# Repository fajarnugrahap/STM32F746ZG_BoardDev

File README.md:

# STM32F746ZG_Minimum-System
There are some embedded features in this minimum system like UART, I2C, CAN Bus, QuadSPI Flash, Ext. SDRAM, SPI for LCD TFT/Oled Support, USB-C and GPIO port                                              

First thing first I set the pinout configuration of STM32F746ZG by using CubeMx tools in STM32CubeIDE
                                                          
I'm using KiCadV6+ to design this minimum system. There is some additional component to support some peripheral/bus. You can check the component library folder.

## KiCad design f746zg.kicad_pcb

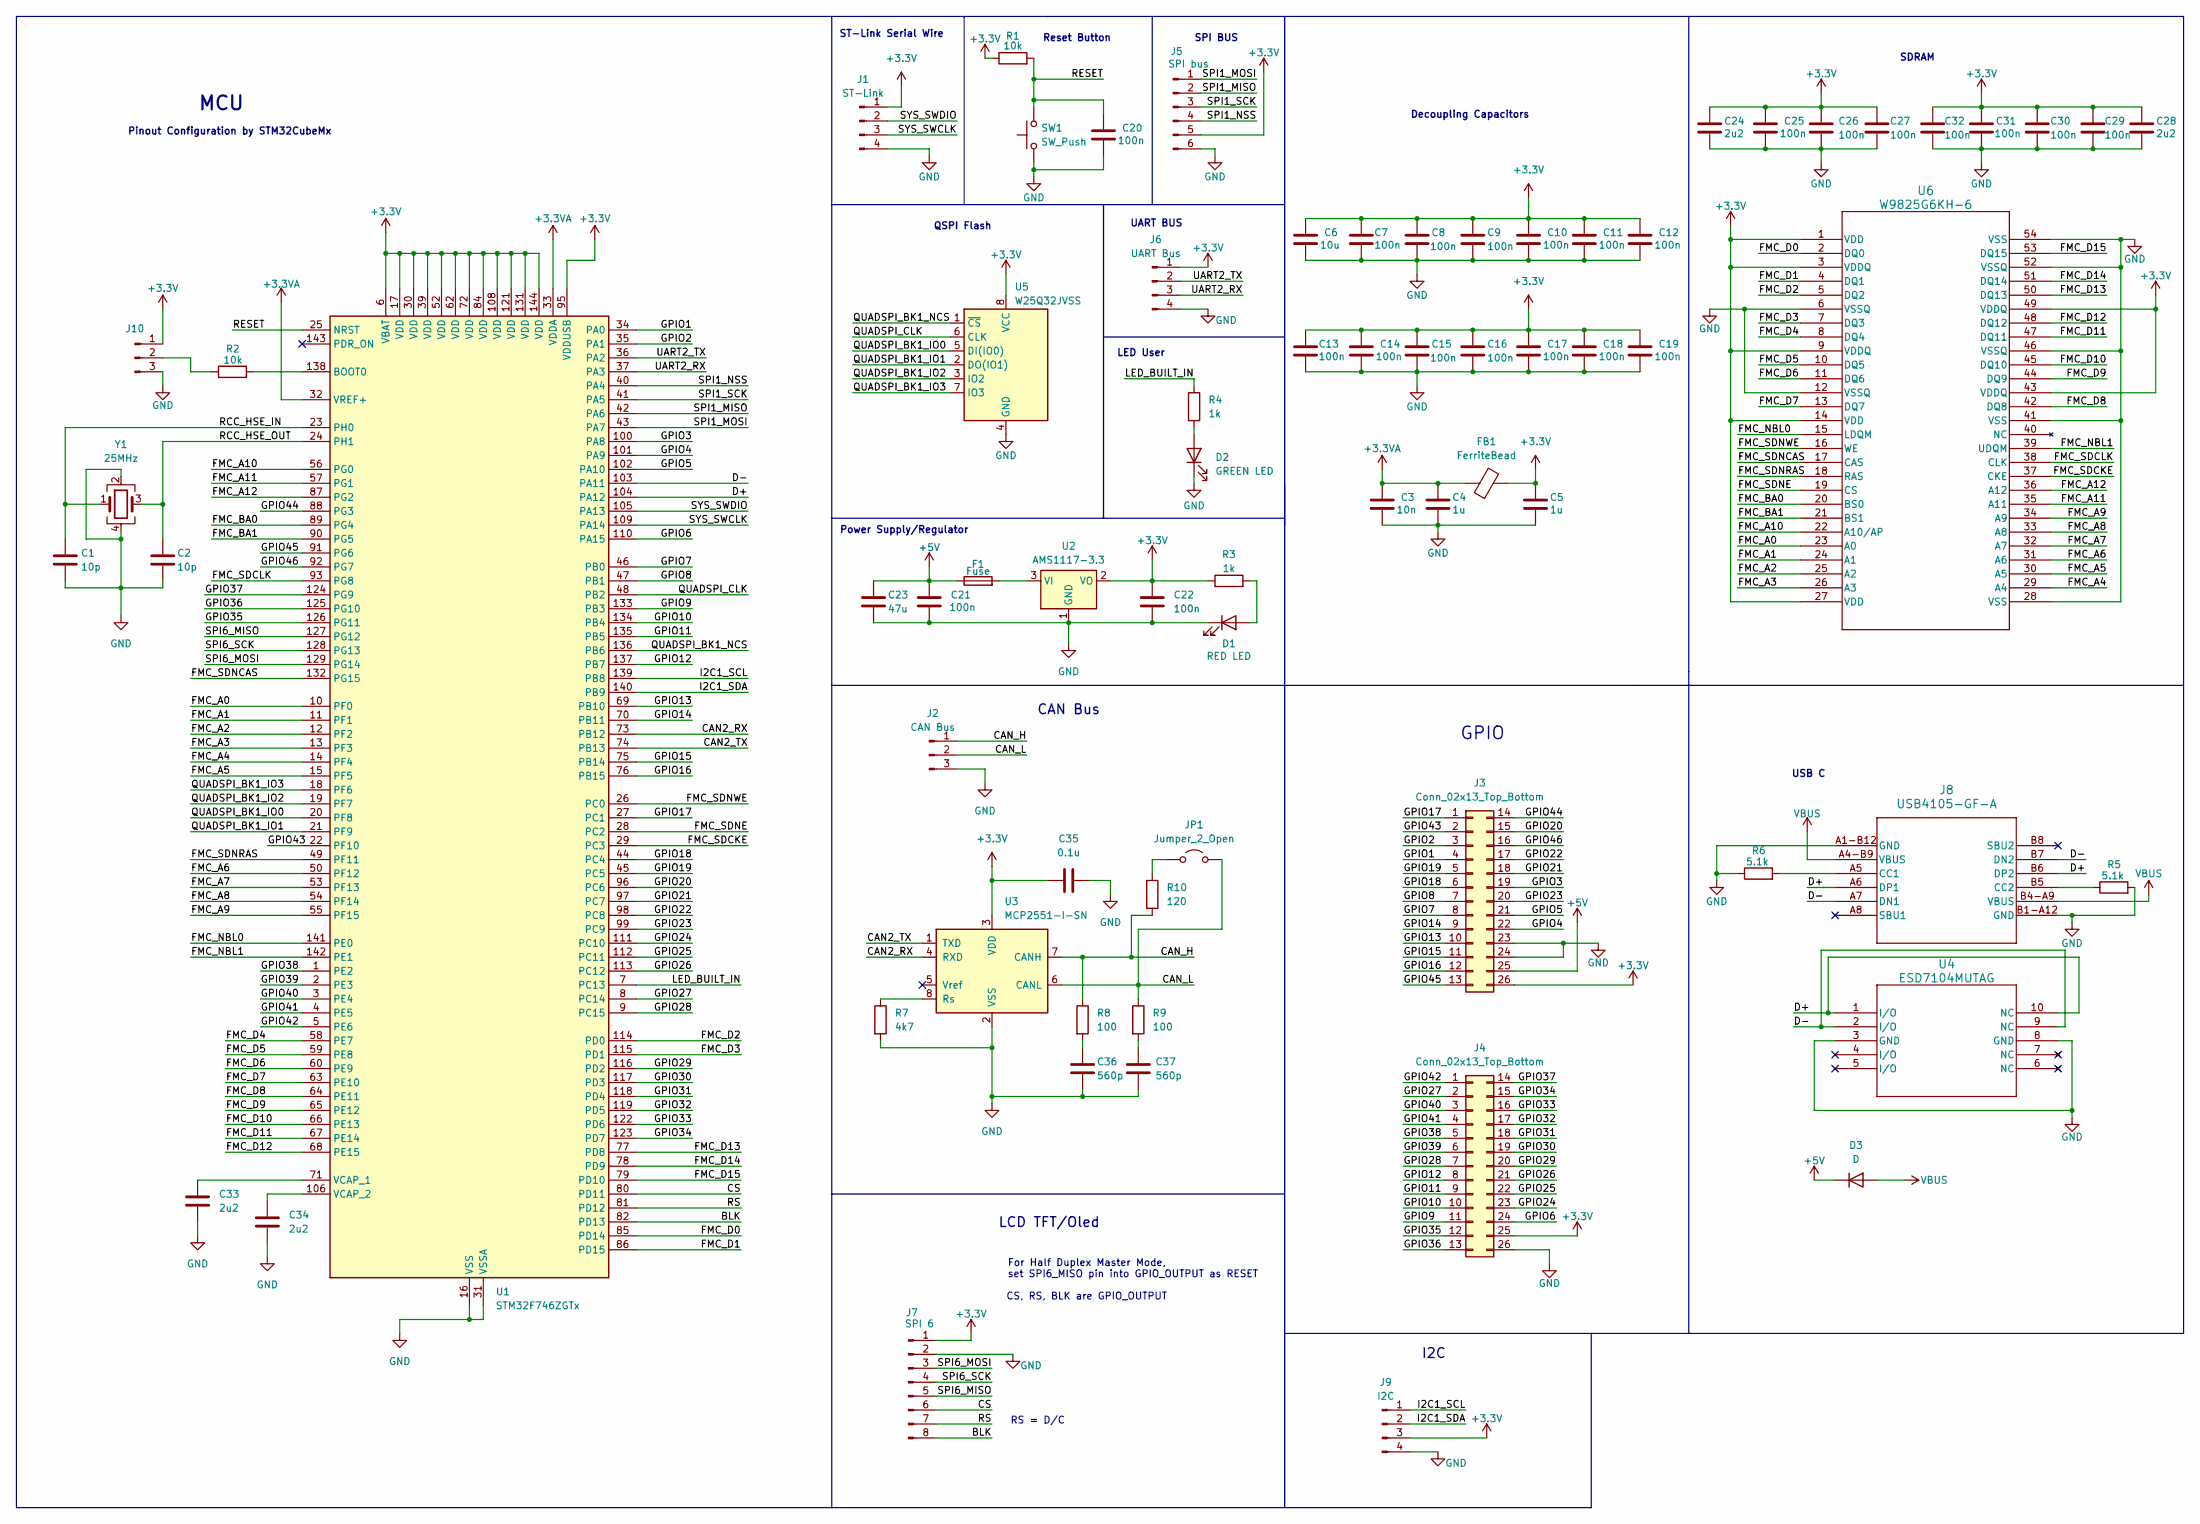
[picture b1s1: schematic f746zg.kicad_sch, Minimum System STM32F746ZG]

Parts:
C1, C2: 10p; C_0402_1005Metric
C3: 10n; C_0402_1005Metric
C4, C5: 1u; C_0603_1608Metric
C6: 10u; C_0805_2012Metric
C7, C8, C9, C10, C11, C12, C13, C14, C15, C16, C17, C18, C19, C20, C21, C22, C25, C26, C27, C29, C30, C31, C32: 100n; C_0402_1005Metric
C23: 47u; C_1206_3216Metric
C24, C28, C33, C34: 2u2; C_0603_1608Metric
C35: 0.1u; C_0402_1005Metric
C36, C37: 560p; C_0402_1005Metric
D1: RED LED; LED_0603_1608Metric
D2: GREEN LED; LED_0603_1608Metric
D3: D; D_SOD-323
F1: Fuse; Fuse_1206_3216Metric_Pad1.42x1.75mm_HandSolder
FB1: FerriteBead; L_0402_1005Metric
J1: ST-Link; PinHeader_1x04_P2.54mm_Vertical
J2: CAN Bus; JST_EH_B3B-EH-A_1x03_P2.50mm_Vertical
J3, J4: Conn_02x13_Top_Bottom; PinHeader_2x13_P2.54mm_Vertical
J5: SPI bus; PinHeader_1x06_P1.27mm_Vertical_SMD_Pin1Left
J6: UART Bus; JST_EH_B4B-EH-A_1x04_P2.50mm_Vertical
J7: SPI 6; PinHeader_1x08_P2.54mm_Vertical
J8: USB4105-GF-A; GCT_USB4105-GF-A
J9: I2C; JST_EH_B4B-EH-A_1x04_P2.50mm_Vertical
J10: Conn_01x03_Pin; PinHeader_1x03_P2.54mm_Vertical
JP1: Jumper_2_Open; PinHeader_1x02_P2.54mm_Vertical
R1, R2: 10k; R_0402_1005Metric
R3, R4: 1k; R_0402_1005Metric
R5, R6: 5.1k; R_0402_1005Metric
R7: 4k7; R_0402_1005Metric
R8, R9: 100; R_0402_1005Metric
R10: 120; R_0402_1005Metric
SW1: SW_Push; SW_Tactile_SPST_NO_Straight_CK_PTS636Sx25SMTRLFS
U1: STM32F746ZGTx; LQFP-144_20x20mm_P0.5mm
U2: AMS1117-3.3; SOT-223-3_TabPin2
U3: MCP2551-I-SN; SOIC-8_3.9x4.9mm_P1.27mm
U4: ESD7104MUTAG; UDFN10_ONS
U5: W25Q32JVSS; SOIC-8_5.23x5.23mm_P1.27mm
U6: W9825G6KH-6; SMT_5G6KH-6_WIN
Y1: 25MHz; Crystal_SMD_3225-4Pin_3.2x2.5mm

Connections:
+3.3V: C5.1, C6.1, C7.1, C8.1, C9.1, C10.1, C11.1, C12.1, C13.1, C14.1, C15.1, C16.1, C17.1, C18.1, C19.1, C22.1, C24.1, C25.1, C26.2, C27.2, C28.1, C29.2, C30.2, C31.1, C32.2, C35.1, FB1.2, J1.1, J3.26, J4.25, J5.5, J6.1, J7.1, J9.3, J10.1, R1.1, R3.1, U1.6 (VBAT), U1.17 (VDD), U1.30 (VDD), U1.39 (VDD), U1.52 (VDD), U1.62 (VDD), U1.72 (VDD), U1.84 (VDD), U1.95 (VDDUSB), U1.108 (VDD), U1.121 (VDD), U1.131 (VDD), U1.144 (VDD), U2.2 (VO), U3.3 (VDD), U5.8 (VCC), U6.1 (VDD), U6.3 (VDDQ), U6.9 (VDDQ), U6.14 (VDD), U6.27 (VDD), U6.43 (VDDQ), U6.49 (VDDQ)
+3.3VA: C3.1, C4.1, FB1.1, U1.32 (VREF+), U1.33 (VDDA)
/BLK: J7.8, U1.82 (PD13)
/CAN2_RX: U1.73 (PB12), U3.4 (RXD)
/CAN2_TX: U1.74 (PB13), U3.1 (TXD)
/CAN_H: J2.1, R8.1, R10.2, U3.7 (CANH)
/CAN_L: J2.2, JP1.2 (B), R9.1, U3.6 (CANL)
/CS: J7.6, U1.80 (PD11)
/D+: J8.A6 (DP1), J8.B6 (DP2), U1.104 (PA12), U4.1 (I/O), U4.10 (NC)
/D-: J8.A7 (DN1), J8.B7 (DN2), U1.103 (PA11), U4.2 (I/O), U4.9 (NC)
/FMC_A0: U1.10 (PF0), U6.23 (A0)
/FMC_A1: U1.11 (PF1), U6.24 (A1)
/FMC_A2: U1.12 (PF2), U6.25 (A2)
/FMC_A3: U1.13 (PF3), U6.26 (A3)
/FMC_A4: U1.14 (PF4), U6.29 (A4)
/FMC_A5: U1.15 (PF5), U6.30 (A5)
/FMC_A6: U1.50 (PF12), U6.31 (A6)
/FMC_A7: U1.53 (PF13), U6.32 (A7)
/FMC_A8: U1.54 (PF14), U6.33 (A8)
/FMC_A9: U1.55 (PF15), U6.34 (A9)
/FMC_A10: U1.56 (PG0), U6.22 (A10/AP)
/FMC_A11: U1.57 (PG1), U6.35 (A11)
/FMC_A12: U1.87 (PG2), U6.36 (A12)
/FMC_BA0: U1.89 (PG4), U6.20 (BS0)
/FMC_BA1: U1.90 (PG5), U6.21 (BS1)
/FMC_D0: U1.85 (PD14), U6.2 (DQ0)
/FMC_D1: U1.86 (PD15), U6.4 (DQ1)
/FMC_D2: U1.114 (PD0), U6.5 (DQ2)
/FMC_D3: U1.115 (PD1), U6.7 (DQ3)
/FMC_D4: U1.58 (PE7), U6.8 (DQ4)
/FMC_D5: U1.59 (PE8), U6.10 (DQ5)
/FMC_D6: U1.60 (PE9), U6.11 (DQ6)
/FMC_D7: U1.63 (PE10), U6.13 (DQ7)
/FMC_D8: U1.64 (PE11), U6.42 (DQ8)
/FMC_D9: U1.65 (PE12), U6.44 (DQ9)
/FMC_D10: U1.66 (PE13), U6.45 (DQ10)
/FMC_D11: U1.67 (PE14), U6.47 (DQ11)
/FMC_D12: U1.68 (PE15), U6.48 (DQ12)
/FMC_D13: U1.77 (PD8), U6.50 (DQ13)
/FMC_D14: U1.78 (PD9), U6.51 (DQ14)
/FMC_D15: U1.79 (PD10), U6.53 (DQ15)
/FMC_NBL0: U1.141 (PE0), U6.15 (LDQM)
/FMC_NBL1: U1.142 (PE1), U6.39 (UDQM)
/FMC_SDCKE: U1.29 (PC3), U6.37 (CKE)
/FMC_SDCLK: U1.93 (PG8), U6.38 (CLK)
/FMC_SDNCAS: U1.132 (PG15), U6.17 (CAS)
/FMC_SDNE: U1.28 (PC2), U6.19 (CS)
/FMC_SDNRAS: U1.49 (PF11), U6.18 (RAS)
/FMC_SDNWE: U1.26 (PC0), U6.16 (WE)
/GPIO1: J3.4, U1.34 (PA0)
/GPIO2: J3.3, U1.35 (PA1)
/GPIO3: J3.19, U1.100 (PA8)
/GPIO4: J3.22, U1.101 (PA9)
/GPIO5: J3.21, U1.102 (PA10)
/GPIO6: J4.24, U1.110 (PA15)
/GPIO7: J3.8, U1.46 (PB0)
/GPIO8: J3.7, U1.47 (PB1)
/GPIO9: J4.11, U1.133 (PB3)
/GPIO10: J4.10, U1.134 (PB4)
/GPIO11: J4.9, U1.135 (PB5)
/GPIO12: J4.8, U1.137 (PB7)
/GPIO13: J3.10, U1.69 (PB10)
/GPIO14: J3.9, U1.70 (PB11)
/GPIO15: J3.11, U1.75 (PB14)
/GPIO16: J3.12, U1.76 (PB15)
/GPIO17: J3.1, U1.27 (PC1)
/GPIO18: J3.6, U1.44 (PC4)
/GPIO19: J3.5, U1.45 (PC5)
/GPIO20: J3.15, U1.96 (PC6)
/GPIO21: J3.18, U1.97 (PC7)
/GPIO22: J3.17, U1.98 (PC8)
/GPIO23: J3.20, U1.99 (PC9)
/GPIO24: J4.23, U1.111 (PC10)
/GPIO25: J4.22, U1.112 (PC11)
/GPIO26: J4.21, U1.113 (PC12)
/GPIO27: J4.2, U1.8 (PC14)
/GPIO28: J4.7, U1.9 (PC15)
/GPIO29: J4.20, U1.116 (PD2)
/GPIO30: J4.19, U1.117 (PD3)
/GPIO31: J4.18, U1.118 (PD4)
/GPIO32: J4.17, U1.119 (PD5)
/GPIO33: J4.16, U1.122 (PD6)
/GPIO34: J4.15, U1.123 (PD7)
/GPIO35: J4.12, U1.126 (PG11)
/GPIO36: J4.13, U1.125 (PG10)
/GPIO37: J4.14, U1.124 (PG9)
/GPIO38: J4.5, U1.1 (PE2)
/GPIO39: J4.6, U1.2 (PE3)
/GPIO40: J4.3, U1.3 (PE4)
/GPIO41: J4.4, U1.4 (PE5)
/GPIO42: J4.1, U1.5 (PE6)
/GPIO43: J3.2, U1.22 (PF10)
/GPIO44: J3.14, U1.88 (PG3)
/GPIO45: J3.13, U1.91 (PG6)
/GPIO46: J3.16, U1.92 (PG7)
/I2C1_SCL: J9.1, U1.139 (PB8)
/I2C1_SDA: J9.2, U1.140 (PB9)
/LED_BUILT_IN: R4.1, U1.7 (PC13)
/QUADSPI_BK1_IO0: U1.20 (PF8), U5.5 (DI(IO0))
/QUADSPI_BK1_IO1: U1.21 (PF9), U5.2 (DO(IO1))
/QUADSPI_BK1_IO2: U1.19 (PF7), U5.3 (IO2)
/QUADSPI_BK1_IO3: U1.18 (PF6), U5.7 (IO3)
/QUADSPI_BK1_NCS: U1.136 (PB6), U5.1 (~CS)
/QUADSPI_CLK: U1.48 (PB2), U5.6 (CLK)
/RCC_HSE_IN: C1.1, U1.23 (PH0), Y1.1
/RCC_HSE_OUT: C2.1, U1.24 (PH1), Y1.3
/RESET: C20.1, R1.2, SW1.2, U1.25 (NRST)
/RS: J7.7, U1.81 (PD12)
/SPI1_MISO: J5.2, U1.42 (PA6)
/SPI1_MOSI: J5.1, U1.43 (PA7)
/SPI1_NSS: J5.4, U1.40 (PA4)
/SPI1_SCK: J5.3, U1.41 (PA5)
/SPI6_MISO: J7.5, U1.127 (PG12)
/SPI6_MOSI: J7.3, U1.129 (PG14)
/SPI6_SCK: J7.4, U1.128 (PG13)
/SYS_SWCLK: J1.3, U1.109 (PA14)
/SYS_SWDIO: J1.2, U1.105 (PA13)
/UART2_RX: J6.3, U1.37 (PA3)
/UART2_TX: J6.2, U1.36 (PA2)
GND: C1.2, C2.2, C3.2, C4.2, C5.2, C6.2, C7.2, C8.2, C9.2, C10.2, C11.2, C12.2, C13.2, C14.2, C15.2, C16.2, C17.2, C18.2, C19.2, C20.2, C21.2, C22.2, C23.2, C24.2, C25.2, C26.1, C27.1, C28.2, C29.1, C30.1, C31.2, C32.1, C33.2, C34.2, C35.2, C36.1, C37.1, D1.1 (K), D2.1 (K), J1.4, J2.3, J3.23, J3.24, J4.26, J5.6, J6.4, J7.2, J8.A1-B12 (GND), J8.A1_B12, J8.B1-A12 (GND), J8.B1_A12, J9.4, J10.3, R5.2, R6.1, R7.2, SW1.1, U1.16 (VSS), U1.31 (VSSA), U1.38 (VSS), U1.51 (VSS), U1.61 (VSS), U1.83 (VSS), U1.94 (VSS), U1.107 (VSS), U1.120 (VSS), U1.130 (VSS), U2.1 (GND), U3.2 (VSS), U4.3 (GND), U4.8 (GND), U5.4 (GND), U6.6 (VSSQ), U6.12 (VSSQ), U6.28 (VSS), U6.41 (VSS), U6.46 (VSSQ), U6.52 (VSSQ), U6.54 (VSS), Y1.2, Y1.4
unnamed: C36.2, R8.2
unnamed: C37.2, R9.2
unnamed: D1.2 (A), R3.2
unnamed: D2.2 (A), R4.2
unnamed: J8.A5 (CC1), R6.2
unnamed: J8.B5 (CC2), R5.1
unnamed: J10.2, R2.1
unnamed: JP1.1 (A), R10.1
unnamed: R2.2, U1.138 (BOOT0)
unnamed: C33.1, U1.71 (VCAP_1)
unnamed: C34.1, U1.106 (VCAP_2)
unnamed: R7.1, U3.8 (Rs)
VBUS: D3.2 (A), J8.A4-B9 (VBUS), J8.A4_B9, J8.B4-A9 (VBUS), J8.B4_A9

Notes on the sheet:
Decoupling Capacitors
QSPI Flash
LED User
SDRAM
UART BUS
RS = D/C
SPI BUS
USB C
CAN Bus
GPIO
Pinout Configuration by STM32CubeMx
For Half Duplex Master Mode, set SPI6_MISO pin into GPIO_OUTPUT as RESET
CS, RS, BLK are GPIO_OUTPUT
ST-Link Serial Wire
Power Supply/Regulator
I2C
Reset Button
LCD TFT/Oled
MCU

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
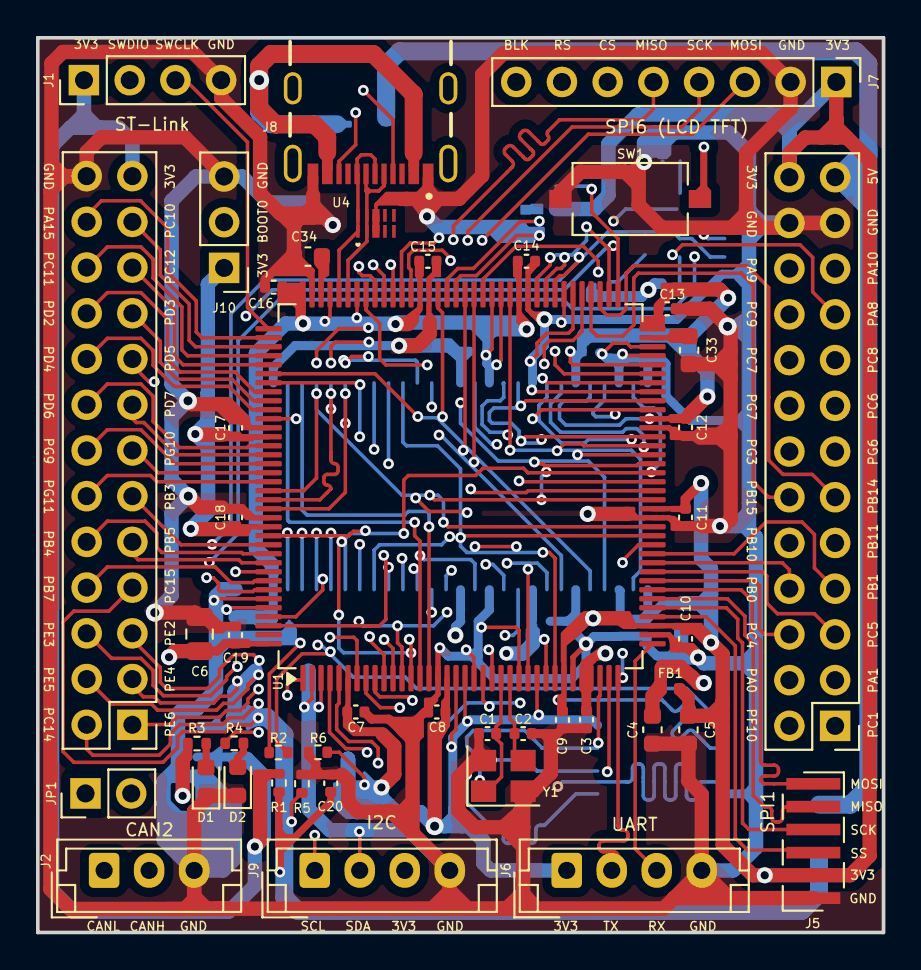
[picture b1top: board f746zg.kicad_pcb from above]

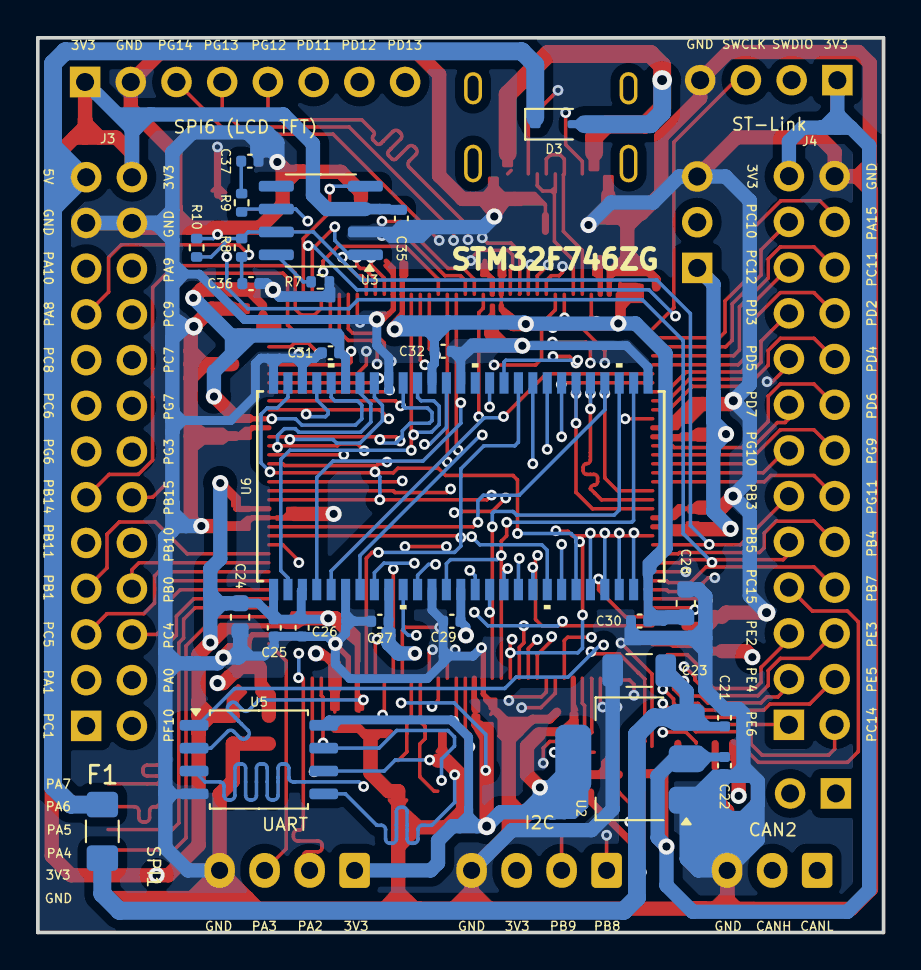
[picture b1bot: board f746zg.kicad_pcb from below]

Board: 4 copper layers, 47.0 x 49.7 mm, 71 parts (25 on the bottom side), 135 nets.

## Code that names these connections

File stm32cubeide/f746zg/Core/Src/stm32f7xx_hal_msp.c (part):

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
    __HAL_RCC_GPIOB_CLK_ENABLE();
    /**CAN2 GPIO Configuration
    PB12     ------> CAN2_RX
    PB13     ------> CAN2_TX
    */
    GPIO_InitStruct.Pin = GPIO_PIN_12|GPIO_PIN_13;
    GPIO_InitStruct.Mode = GPIO_MODE_AF_PP;
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    __HAL_RCC_CAN1_CLK_DISABLE();

    /**CAN2 GPIO Configuration
    PB12     ------> CAN2_RX
    PB13     ------> CAN2_TX
    */
    HAL_GPIO_DeInit(GPIOB, GPIO_PIN_12|GPIO_PIN_13);

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
    __HAL_RCC_GPIOB_CLK_ENABLE();
    /**I2C1 GPIO Configuration
    PB7     ------> I2C1_SDA
    PB8     ------> I2C1_SCL
    */
    GPIO_InitStruct.Pin = GPIO_PIN_7|GPIO_PIN_8;
    GPIO_InitStruct.Mode = GPIO_MODE_AF_OD;
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    __HAL_RCC_I2C1_CLK_DISABLE();

    /**I2C1 GPIO Configuration
    PB7     ------> I2C1_SDA
    PB8     ------> I2C1_SCL
    */
    HAL_GPIO_DeInit(GPIOB, GPIO_PIN_7);

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    __HAL_RCC_GPIOF_CLK_ENABLE();
    __HAL_RCC_GPIOB_CLK_ENABLE();
    /**QUADSPI GPIO Configuration
    PF6     ------> QUADSPI_BK1_IO3
    PF7     ------> QUADSPI_BK1_IO2
    PF8     ------> QUADSPI_BK1_IO0
    PF9     ------> QUADSPI_BK1_IO1
    PB2     ------> QUADSPI_CLK
    PB6     ------> QUADSPI_BK1_NCS
    */
    GPIO_InitStruct.Pin = GPIO_PIN_6|GPIO_PIN_7;
    GPIO_InitStruct.Mode = GPIO_MODE_AF_PP;
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    __HAL_RCC_QSPI_CLK_DISABLE();

    /**QUADSPI GPIO Configuration
    PF6     ------> QUADSPI_BK1_IO3
    PF7     ------> QUADSPI_BK1_IO2
    PF8     ------> QUADSPI_BK1_IO0
    PF9     ------> QUADSPI_BK1_IO1
    PB2     ------> QUADSPI_CLK
    PB6     ------> QUADSPI_BK1_NCS
    */
    HAL_GPIO_DeInit(GPIOF, GPIO_PIN_6|GPIO_PIN_7|GPIO_PIN_8|GPIO_PIN_9);

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    __HAL_RCC_GPIOA_CLK_ENABLE();
    __HAL_RCC_GPIOB_CLK_ENABLE();
    /**SPI1 GPIO Configuration
    PA4     ------> SPI1_NSS
    PA5     ------> SPI1_SCK
    PA6     ------> SPI1_MISO
    PB5     ------> SPI1_MOSI
    */
    GPIO_InitStruct.Pin = GPIO_PIN_4|GPIO_PIN_5|GPIO_PIN_6;
    GPIO_InitStruct.Mode = GPIO_MODE_AF_PP;
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    __HAL_RCC_SPI1_CLK_DISABLE();

    /**SPI1 GPIO Configuration
    PA4     ------> SPI1_NSS
    PA5     ------> SPI1_SCK
    PA6     ------> SPI1_MISO
    PB5     ------> SPI1_MOSI
    */
    HAL_GPIO_DeInit(GPIOA, GPIO_PIN_4|GPIO_PIN_5|GPIO_PIN_6);

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
    __HAL_RCC_GPIOA_CLK_ENABLE();
    /**UART4 GPIO Configuration
    PA0/WKUP     ------> UART4_TX
    PA1     ------> UART4_RX
    */
    GPIO_InitStruct.Pin = GPIO_PIN_0|GPIO_PIN_1;
    GPIO_InitStruct.Mode = GPIO_MODE_AF_PP;
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    __HAL_RCC_UART4_CLK_DISABLE();

    /**UART4 GPIO Configuration
    PA0/WKUP     ------> UART4_TX
    PA1     ------> UART4_RX
    */
    HAL_GPIO_DeInit(GPIOA, GPIO_PIN_0|GPIO_PIN_1);

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
    __HAL_RCC_GPIOA_CLK_ENABLE();
    /**USB_OTG_FS GPIO Configuration
    PA8     ------> USB_OTG_FS_SOF
    PA9     ------> USB_OTG_FS_VBUS
    PA10     ------> USB_OTG_FS_ID
    PA11     ------> USB_OTG_FS_DM
    PA12     ------> USB_OTG_FS_DP
    */
    GPIO_InitStruct.Pin = GPIO_PIN_8|GPIO_PIN_10|GPIO_PIN_11|GPIO_PIN_12;
    GPIO_InitStruct.Mode = GPIO_MODE_AF_PP;
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    __HAL_RCC_USB_OTG_FS_CLK_DISABLE();

    /**USB_OTG_FS GPIO Configuration
    PA8     ------> USB_OTG_FS_SOF
    PA9     ------> USB_OTG_FS_VBUS
    PA10     ------> USB_OTG_FS_ID
    PA11     ------> USB_OTG_FS_DM
    PA12     ------> USB_OTG_FS_DP
    */
    HAL_GPIO_DeInit(GPIOA, GPIO_PIN_8|GPIO_PIN_9|GPIO_PIN_10|GPIO_PIN_11
                          |GPIO_PIN_12);
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  __HAL_RCC_FMC_CLK_ENABLE();

  /** FMC GPIO Configuration
  PF0   ------> FMC_A0
  PF1   ------> FMC_A1
  PF2   ------> FMC_A2
  PF3   ------> FMC_A3
  PF4   ------> FMC_A4
  PF5   ------> FMC_A5
  PC0   ------> FMC_SDNWE
  PC2   ------> FMC_SDNE0
  PC3   ------> FMC_SDCKE0
  PF11   ------> FMC_SDNRAS
  PF12   ------> FMC_A6
  PF13   ------> FMC_A7
  PF14   ------> FMC_A8
  PF15   ------> FMC_A9
  PG0   ------> FMC_A10
  PG1   ------> FMC_A11
  PE7   ------> FMC_D4
  PE8   ------> FMC_D5
  PE9   ------> FMC_D6
  PE10   ------> FMC_D7
  PE11   ------> FMC_D8
  PE12   ------> FMC_D9
  PE13   ------> FMC_D10
  PE14   ------> FMC_D11
  PE15   ------> FMC_D12
  PD8   ------> FMC_D13
  PD9   ------> FMC_D14
  PD10   ------> FMC_D15
  PD14   ------> FMC_D0
  PD15   ------> FMC_D1
  PG2   ------> FMC_A12
  PG4   ------> FMC_BA0
  PG5   ------> FMC_BA1
  PG8   ------> FMC_SDCLK
  PD0   ------> FMC_D2
  PD1   ------> FMC_D3
  PG15   ------> FMC_SDNCAS
  PE0   ------> FMC_NBL0
  PE1   ------> FMC_NBL1
  */
  GPIO_InitStruct.Pin = GPIO_PIN_0|GPIO_PIN_1|GPIO_PIN_2|GPIO_PIN_3
                          |GPIO_PIN_4|GPIO_PIN_5|GPIO_PIN_11|GPIO_PIN_12
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  __HAL_RCC_FMC_CLK_DISABLE();

  /** FMC GPIO Configuration
  PF0   ------> FMC_A0
  PF1   ------> FMC_A1
  PF2   ------> FMC_A2
  PF3   ------> FMC_A3
  PF4   ------> FMC_A4
  PF5   ------> FMC_A5
  PC0   ------> FMC_SDNWE
  PC2   ------> FMC_SDNE0
  PC3   ------> FMC_SDCKE0
  PF11   ------> FMC_SDNRAS
  PF12   ------> FMC_A6
  PF13   ------> FMC_A7
  PF14   ------> FMC_A8
  PF15   ------> FMC_A9
  PG0   ------> FMC_A10
  PG1   ------> FMC_A11
  PE7   ------> FMC_D4
  PE8   ------> FMC_D5
  PE9   ------> FMC_D6
  PE10   ------> FMC_D7
  PE11   ------> FMC_D8
  PE12   ------> FMC_D9
  PE13   ------> FMC_D10
  PE14   ------> FMC_D11
  PE15   ------> FMC_D12
  PD8   ------> FMC_D13
  PD9   ------> FMC_D14
  PD10   ------> FMC_D15
  PD14   ------> FMC_D0
  PD15   ------> FMC_D1
  PG2   ------> FMC_A12
  PG4   ------> FMC_BA0
  PG5   ------> FMC_BA1
  PG8   ------> FMC_SDCLK
  PD0   ------> FMC_D2
  PD1   ------> FMC_D3
  PG15   ------> FMC_SDNCAS
  PE0   ------> FMC_NBL0
  PE1   ------> FMC_NBL1
  */
  HAL_GPIO_DeInit(GPIOF, GPIO_PIN_0|GPIO_PIN_1|GPIO_PIN_2|GPIO_PIN_3
                          |GPIO_PIN_4|GPIO_PIN_5|GPIO_PIN_11|GPIO_PIN_12
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
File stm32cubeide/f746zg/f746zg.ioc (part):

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Mcu.Name=STM32F746ZGTx
Mcu.Package=LQFP144
Mcu.UserName=STM32F746ZGTx
PA0/WKUP.Mode=Asynchronous
PA0/WKUP.Signal=UART4_TX
PA1.Mode=Asynchronous
PA1.Signal=UART4_RX
PA10.Signal=USB_OTG_FS_ID
PA11.Mode=Device_Only
PA11.Signal=USB_OTG_FS_DM
PA12.Mode=Device_Only
PA12.Signal=USB_OTG_FS_DP
PA13.Mode=Serial_Wire
PA13.Signal=SYS_JTMS-SWDIO
PA14.Mode=Serial_Wire
PA14.Signal=SYS_JTCK-SWCLK
PA4.Mode=NSS_Signal_Hard_Input
PA4.Signal=SPI1_NSS
PA5.Mode=Full_Duplex_Master
PA5.Signal=SPI1_SCK
PA6.Mode=Full_Duplex_Master
PA6.Signal=SPI1_MISO
PA8.Mode=Activate_SOF_FS
PA8.Signal=USB_OTG_FS_SOF
PA9.Mode=Activate_VBUS
PA9.Signal=USB_OTG_FS_VBUS
PB12.Mode=CAN_Activate
PB12.Signal=CAN2_RX
PB13.Mode=CAN_Activate
PB13.Signal=CAN2_TX
PB2.Mode=Single Bank 1
PB2.Signal=QUADSPI_CLK
PB5.Mode=Full_Duplex_Master
PB5.Signal=SPI1_MOSI
PB6.Mode=Single Bank 1
PB6.Signal=QUADSPI_BK1_NCS
PB7.Mode=I2C
PB7.Signal=I2C1_SDA
PB8.Mode=I2C
PB8.Signal=I2C1_SCL
PC0.Signal=FMC_SDNWE
PC13.Signal=GPIO_Output
PC2.Mode=SdramChipSelect1_1
PC2.Signal=FMC_SDNE0
PC3.Mode=SdramChipSelect1_1
PC3.Signal=FMC_SDCKE0
PD0.Signal=FMC_D2_DA2
PD1.Signal=FMC_D3_DA3
PD10.Signal=FMC_D15_DA15
PD14.Signal=FMC_D0_DA0
PD15.Signal=FMC_D1_DA1
PD8.Signal=FMC_D13_DA13
PD9.Signal=FMC_D14_DA14
PE0.Signal=FMC_NBL0
PE1.Signal=FMC_NBL1
PE10.Signal=FMC_D7_DA7
PE11.Signal=FMC_D8_DA8
PE12.Signal=FMC_D9_DA9
PE13.Signal=FMC_D10_DA10
PE14.Signal=FMC_D11_DA11
PE15.Signal=FMC_D12_DA12
PE7.Signal=FMC_D4_DA4
PE8.Signal=FMC_D5_DA5
PE9.Signal=FMC_D6_DA6
PF0.Signal=FMC_A0
PF1.Signal=FMC_A1
PF11.Signal=FMC_SDNRAS
PF12.Signal=FMC_A6
PF13.Signal=FMC_A7
PF14.Signal=FMC_A8
PF15.Signal=FMC_A9
PF2.Signal=FMC_A2
PF3.Signal=FMC_A3
PF4.Signal=FMC_A4
PF5.Signal=FMC_A5
PF6.Mode=Single Bank 1
PF6.Signal=QUADSPI_BK1_IO3
PF7.Mode=Single Bank 1
PF7.Signal=QUADSPI_BK1_IO2
PF8.Mode=Single Bank 1
PF8.Signal=QUADSPI_BK1_IO0
PF9.Mode=Single Bank 1
PF9.Signal=QUADSPI_BK1_IO1
PG0.Signal=FMC_A10
PG1.Signal=FMC_A11
PG15.Signal=FMC_SDNCAS
PG2.Signal=FMC_A12
PG4.Signal=FMC_A14_BA0
PG5.Signal=FMC_A15_BA1
PG8.Signal=FMC_SDCLK
PH0/OSC_IN.Mode=HSE-External-Oscillator
PH0/OSC_IN.Signal=RCC_OSC_IN
PH1/OSC_OUT.Mode=HSE-External-Oscillator
PH1/OSC_OUT.Signal=RCC_OSC_OUT
RCC.HSE_VALUE=16000000
RCC.SYSCLKFreq_VALUE=216000000
RCC.SYSCLKSource=RCC_SYSCLKSOURCE_PLLCLK
board=custom

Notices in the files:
stm32cubeide/f746zg/Core/Src/stm32f7xx_hal_msp.c:
Copyright (c) 2024 STMicroelectronics.
All rights reserved.
This software is licensed under terms that can be found in the LICENSE file
